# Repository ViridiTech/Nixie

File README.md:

# Nixie
 4 digit nixie clock on IN-12 lamps
 
</a>

General schematic inculed most important components:

</a>

Brain of the clock is [ESP32-C3 Super Mini](https://allegro.pl/events/clicks?emission_unit_id=f06a5ec8-8059-49f5-b3e1-0427a0f30828&emission_id=fa8220df-9dc3-44b3-8bd5-d7bab4bfcdd1&type=OFFER&ts=1741079374214&redirect=https%3A%2F%2Fallegro.pl%2Foferta%2Fesp32-c3-super-mini-wifi-bluetooth-ble-5-0-nastepca-esp8266-d1-mini-15295513744%3Fbi_s%3Dads%26bi_m%3Dproductlisting%253Adesktop%253Aquery%26bi_c%3DYjM1MWQ2YjgtZmRkYS00ZTU5LWE4YWEtZmFkNTI4YTliM2E3AA%26bi_t%3Dape&placement=productlisting:desktop:query&sig=47fc114a77d64e92962a4eec50b8c331).

ICs used:

- two 74HC959 shift registers,

- four nixie lamp drivers: K155ID1 and SN74141N both work the same and have the same I/O.

Four IN-12 display time. Both A and B variants could be used.

Seconds indicator is taken from probe screwdriver, typical neon indicator (gas-discharge lamp) can be used.

Seconds indicator is driven by 5V relay (transistor-diode control to ensure no damage to microcontroler should be used, or alternatively for DIY solution Arduino relay module can be used).

Nixie lamps require 170V power supply to be used, I chose [this one](https://pl.aliexpress.com/item/1005005721193065.html?src=google&pdp_npi=4%40dis!PLN!15.17!11.59!!!!!%40!12000034113964492!ppc!!!&src=google&albch=shopping&acnt=708-803-3821&isdl=y&slnk=&plac=&mtctp=&albbt=Google_7_shopping&aff_platform=google&aff_short_key=UneMJZVf&gclsrc=aw.ds&&albagn=888888&&ds_e_adid=&ds_e_matchtype=&ds_e_device=c&ds_e_network=x&ds_e_product_group_id=&ds_e_product_id=pl1005005721193065&ds_e_product_merchant_id=107726890&ds_e_product_country=PL&ds_e_product_language=pl&ds_e_product_channel=online&ds_e_product_store_id=&ds_url_v=2&albcp=19735245762&albag=&isSmbAutoCall=false&needSmbHouyi=false&gad_source=1&gclid=CjwKCAiA5pq-BhBuEiwAvkzVZf3OkaujjkBrAG5RaLtoEE9kd9NwcMxYW9DeDCp0z5XIMhVfqe0_oxoCYh0QAvD_BwE).

# IMPORTANT
You have to program ESP32 yourself using Arduino IDE or other ESP-compatible environment using NIXIE_clock directory.

In the code you MUST MODIFY WiFi settings to allow the clock to connect to the Internet.

# DISCLAIMER
The current code has not been tested on current version of hardware.

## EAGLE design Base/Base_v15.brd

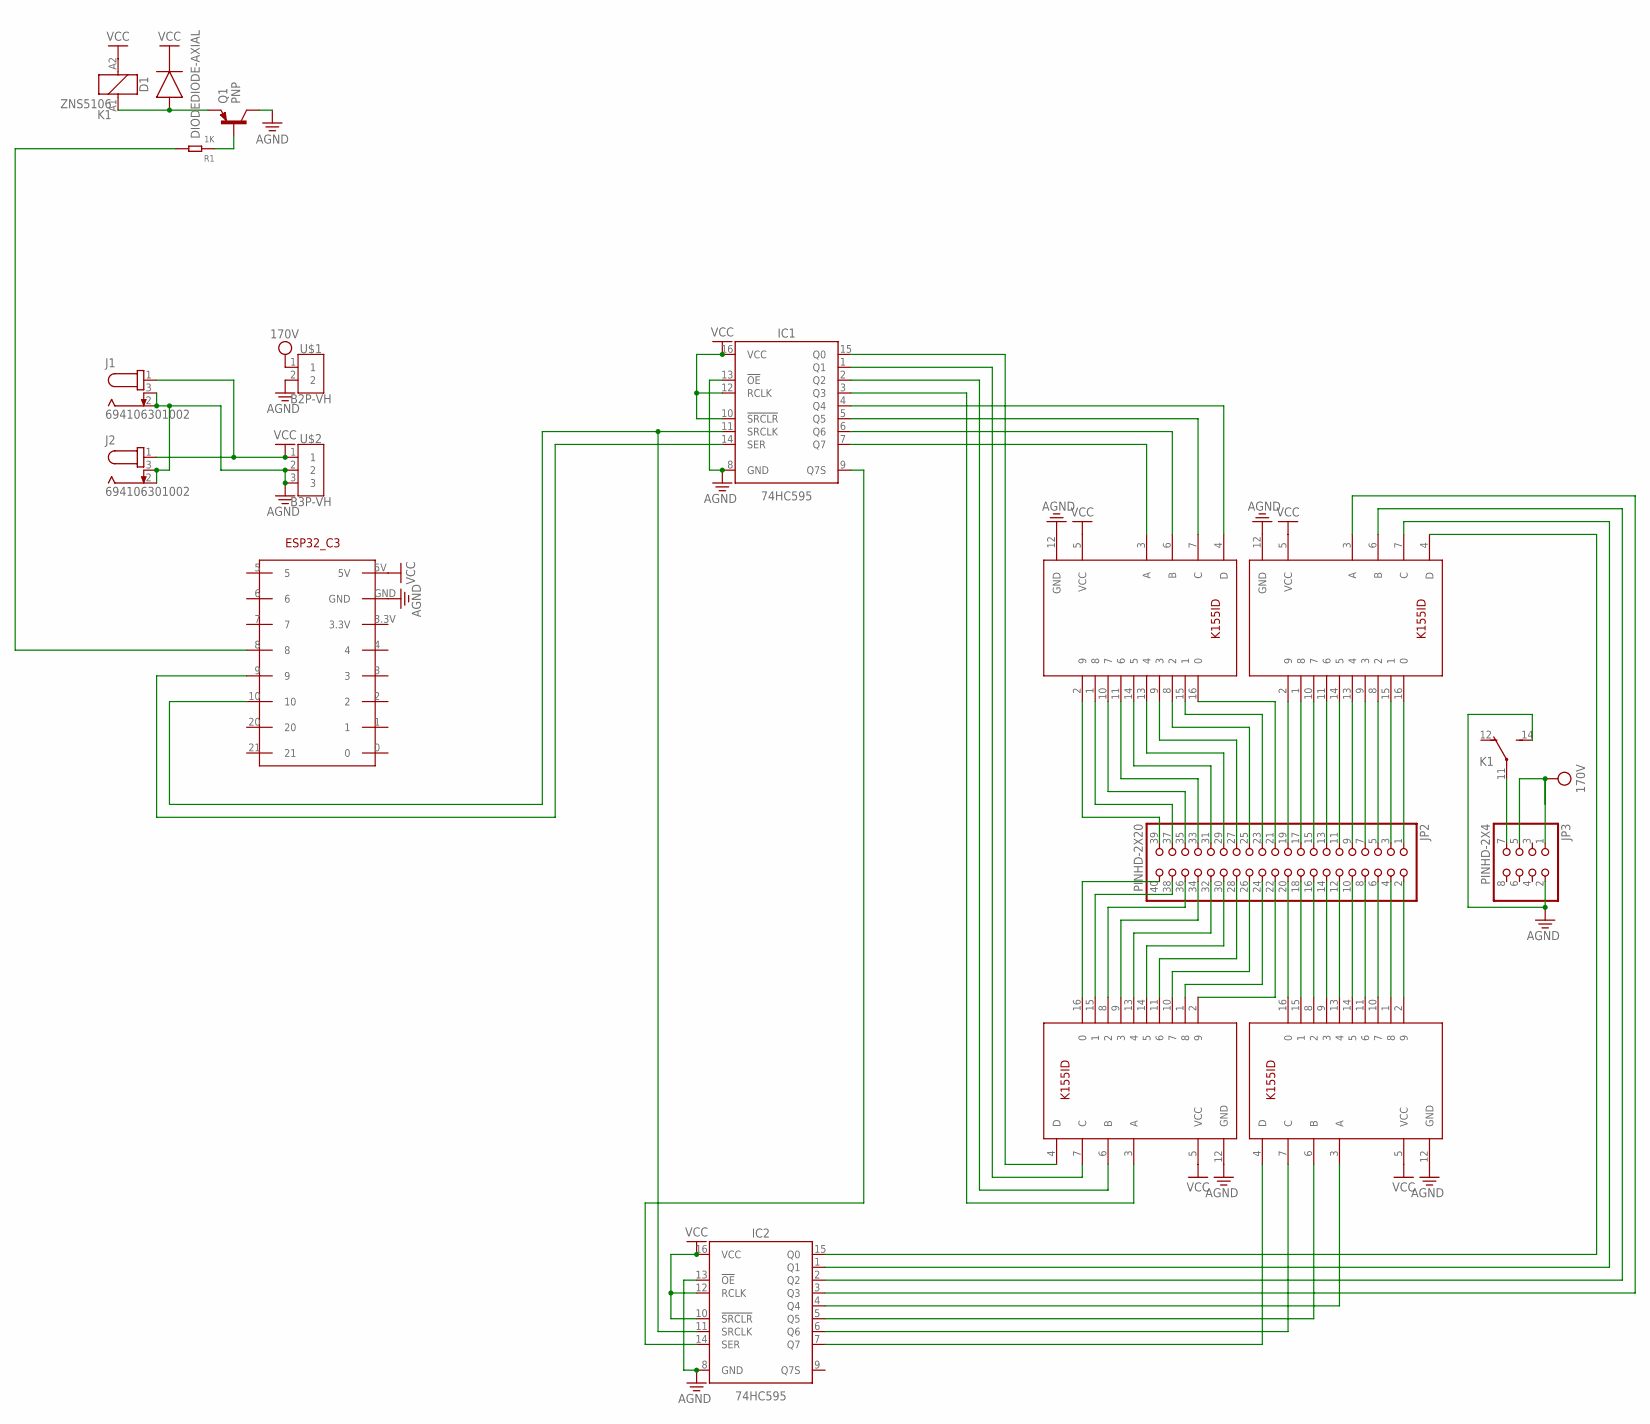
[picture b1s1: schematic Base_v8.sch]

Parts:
D1: DIODEDIODE-AXIAL; DIODE-AXIAL
IC1, IC2: 74HC595; DIP762W53P254L1969H508Q16B
IC3, IC4, IC5, IC6: K155ID
J1, J2: 694106301002
JP2: PINHD-2X20; 2X20
JP3: PINHD-2X4; 2X04
K1: ZNS5106; ZN5
Q1: PNP; TO92
R1: 1K; PR-D2.3XL6.5MM
U$1: B2P-VH; B2P-VH_396-2N
U$2: B3P-VH; B3P-VH_396_3N
U$5: ESP32_C3_SUPERMINI

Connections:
170V: JP3.1, JP3.5, U$1.1
AGND: IC1.8 (GND), IC1.13 (!OE), IC2.8 (GND), IC2.13 (!OE), IC3.12 (GND), IC4.12 (GND), IC5.12 (GND), IC6.12 (GND), J1.2, J1.3, J2.2, J2.3, JP3.2, K1.14 (S), Q1.1 (C), U$1.2, U$2.2, U$2.3, U$5.GND
unnamed: IC5.16 (0), JP2.1
unnamed: IC5.15 (1), JP2.3
unnamed: IC5.8 (2), JP2.5
unnamed: IC5.9 (3), JP2.7
unnamed: IC5.13 (4), JP2.9
unnamed: IC5.14 (5), JP2.11
unnamed: IC5.11 (6), JP2.13
unnamed: IC5.10 (7), JP2.15
unnamed: IC5.1 (8), JP2.17
unnamed: IC5.2 (9), JP2.19
unnamed: IC3.16 (0), JP2.21
unnamed: IC3.15 (1), JP2.23
unnamed: IC3.8 (2), JP2.25
unnamed: IC3.9 (3), JP2.27
unnamed: IC3.13 (4), JP2.29
unnamed: IC3.14 (5), JP2.31
unnamed: IC3.11 (6), JP2.33
unnamed: IC3.10 (7), JP2.35
unnamed: IC3.1 (8), JP2.37
unnamed: IC3.2 (9), JP2.39
unnamed: IC6.2 (9), JP2.2
unnamed: IC6.1 (8), JP2.4
unnamed: IC6.10 (7), JP2.6
unnamed: IC6.11 (6), JP2.8
unnamed: IC6.14 (5), JP2.10
unnamed: IC6.13 (4), JP2.12
unnamed: IC6.9 (3), JP2.14
unnamed: IC6.8 (2), JP2.16
unnamed: IC6.15 (1), JP2.18
unnamed: IC6.16 (0), JP2.20
unnamed: IC4.16 (0), JP2.40
unnamed: IC4.15 (1), JP2.38
unnamed: IC4.8 (2), JP2.36
unnamed: IC4.9 (3), JP2.34
unnamed: IC4.13 (4), JP2.32
unnamed: IC4.14 (5), JP2.30
unnamed: IC4.11 (6), JP2.28
unnamed: IC4.10 (7), JP2.26
unnamed: IC4.1 (8), JP2.24
unnamed: IC4.2 (9), JP2.22
unnamed: IC1.15 (Q0), IC4.4 (D)
unnamed: IC1.1 (Q1), IC4.7 (C)
unnamed: IC1.2 (Q2), IC4.6 (B)
unnamed: IC1.3 (Q3), IC4.3 (A)
unnamed: IC2.4 (Q4), IC6.3 (A)
unnamed: IC2.5 (Q5), IC6.6 (B)
unnamed: IC2.6 (Q6), IC6.7 (C)
unnamed: IC2.7 (Q7), IC6.4 (D)
unnamed: IC1.7 (Q7), IC3.3 (A)
unnamed: IC1.6 (Q6), IC3.6 (B)
unnamed: IC1.5 (Q5), IC3.7 (C)
unnamed: IC1.4 (Q4), IC3.4 (D)
unnamed: IC2.15 (Q0), IC5.4 (D)
unnamed: IC2.1 (Q1), IC5.7 (C)
unnamed: IC2.2 (Q2), IC5.6 (B)
unnamed: IC2.3 (Q3), IC5.3 (A)
unnamed: IC1.9 (Q7S), IC2.14 (SER)
unnamed: IC1.14 (SER), U$5.9
unnamed: D1.1 (A), K1.A1 (1), Q1.3 (E)
unnamed: Q1.2 (B), R1.1
unnamed: R1.2, U$5.8
unnamed: JP3.7, K1.11

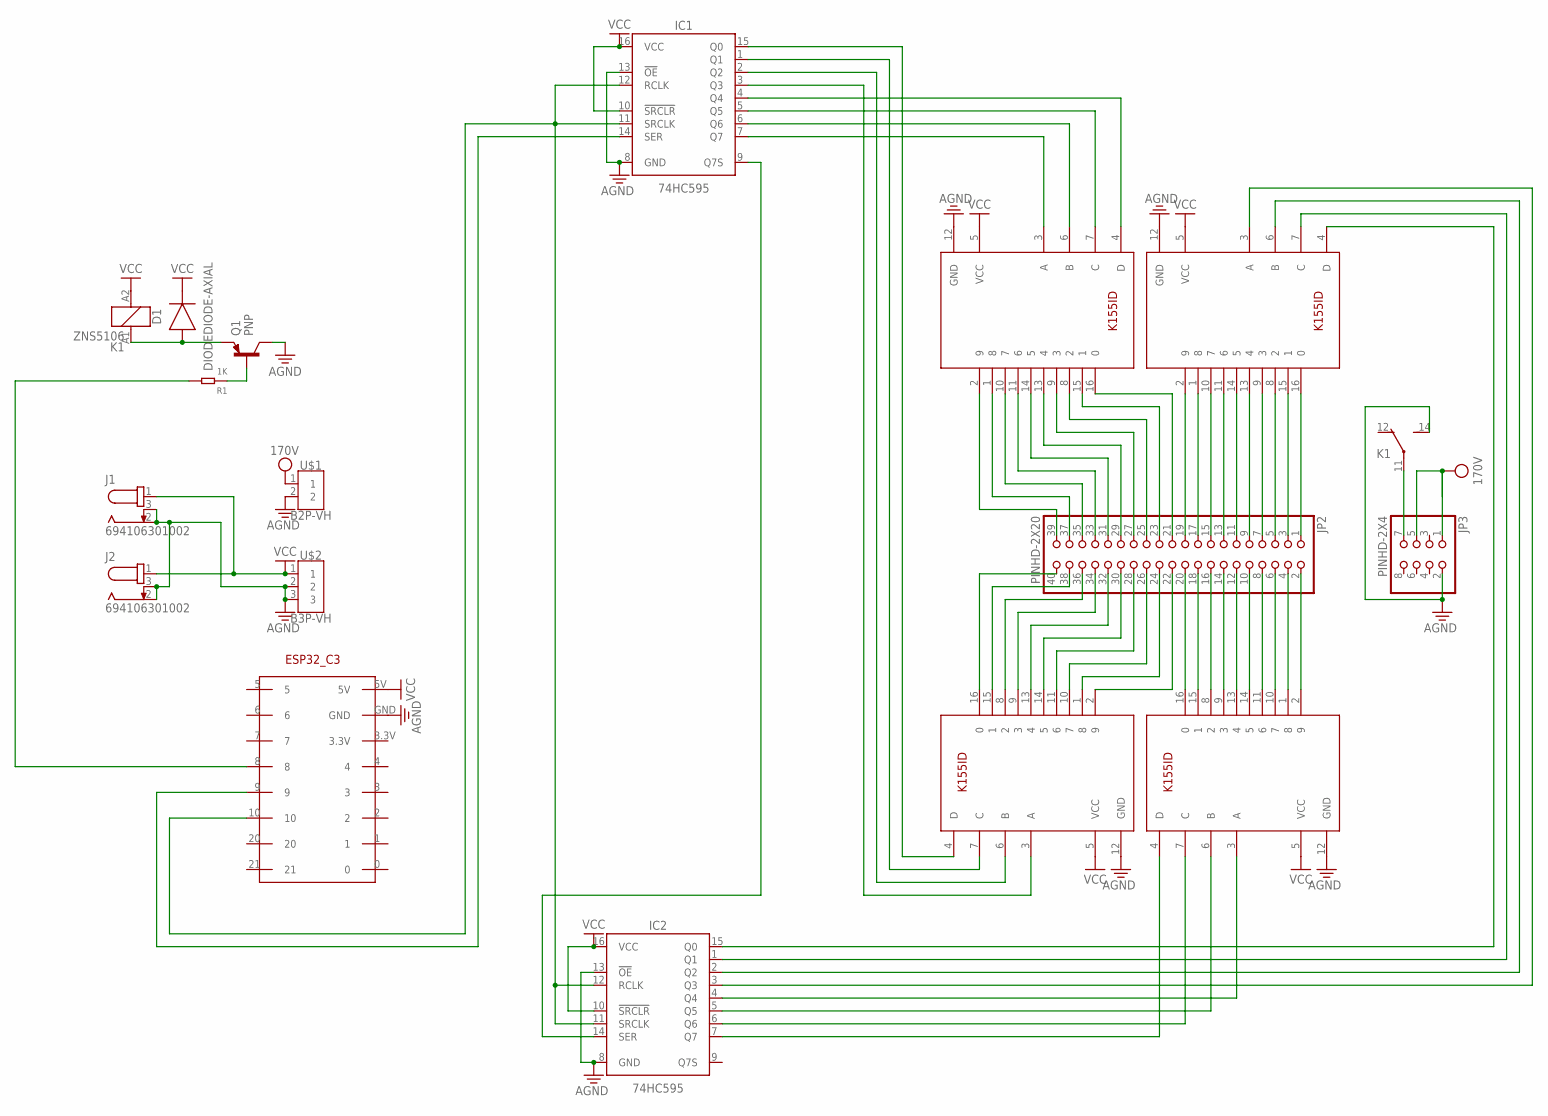
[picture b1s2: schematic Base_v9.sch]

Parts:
D1: DIODEDIODE-AXIAL; DIODE-AXIAL
IC1, IC2: 74HC595; DIP762W53P254L1969H508Q16B
IC3, IC4, IC5, IC6: K155ID
J1, J2: 694106301002
JP2: PINHD-2X20; 2X20
JP3: PINHD-2X4; 2X04
K1: ZNS5106; ZN5
Q1: PNP; TO92
R1: 1K; PR-D2.3XL6.5MM
U$1: B2P-VH; B2P-VH_396-2N
U$2: B3P-VH; B3P-VH_396_3N
U$5: ESP32_C3_SUPERMINI

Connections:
170V: JP3.1, JP3.5, U$1.1
AGND: IC1.8 (GND), IC1.13 (!OE), IC2.8 (GND), IC2.13 (!OE), IC3.12 (GND), IC4.12 (GND), IC5.12 (GND), IC6.12 (GND), J1.2, J1.3, J2.2, J2.3, JP3.2, K1.14 (S), Q1.1 (C), U$1.2, U$2.2, U$2.3, U$5.GND
unnamed: IC5.16 (0), JP2.1
unnamed: IC5.15 (1), JP2.3
unnamed: IC5.8 (2), JP2.5
unnamed: IC5.9 (3), JP2.7
unnamed: IC5.13 (4), JP2.9
unnamed: IC5.14 (5), JP2.11
unnamed: IC5.11 (6), JP2.13
unnamed: IC5.10 (7), JP2.15
unnamed: IC5.1 (8), JP2.17
unnamed: IC5.2 (9), JP2.19
unnamed: IC3.16 (0), JP2.21
unnamed: IC3.15 (1), JP2.23
unnamed: IC3.8 (2), JP2.25
unnamed: IC3.9 (3), JP2.27
unnamed: IC3.13 (4), JP2.29
unnamed: IC3.14 (5), JP2.31
unnamed: IC3.11 (6), JP2.33
unnamed: IC3.10 (7), JP2.35
unnamed: IC3.1 (8), JP2.37
unnamed: IC3.2 (9), JP2.39
unnamed: IC6.2 (9), JP2.2
unnamed: IC6.1 (8), JP2.4
unnamed: IC6.10 (7), JP2.6
unnamed: IC6.11 (6), JP2.8
unnamed: IC6.14 (5), JP2.10
unnamed: IC6.13 (4), JP2.12
unnamed: IC6.9 (3), JP2.14
unnamed: IC6.8 (2), JP2.16
unnamed: IC6.15 (1), JP2.18
unnamed: IC6.16 (0), JP2.20
unnamed: IC4.16 (0), JP2.40
unnamed: IC4.15 (1), JP2.38
unnamed: IC4.8 (2), JP2.36
unnamed: IC4.9 (3), JP2.34
unnamed: IC4.13 (4), JP2.32
unnamed: IC4.14 (5), JP2.30
unnamed: IC4.11 (6), JP2.28
unnamed: IC4.10 (7), JP2.26
unnamed: IC4.1 (8), JP2.24
unnamed: IC4.2 (9), JP2.22
unnamed: IC1.15 (Q0), IC4.4 (D)
unnamed: IC1.1 (Q1), IC4.7 (C)
unnamed: IC1.2 (Q2), IC4.6 (B)
unnamed: IC1.3 (Q3), IC4.3 (A)
unnamed: IC2.4 (Q4), IC6.3 (A)
unnamed: IC2.5 (Q5), IC6.6 (B)
unnamed: IC2.6 (Q6), IC6.7 (C)
unnamed: IC2.7 (Q7), IC6.4 (D)
unnamed: IC1.7 (Q7), IC3.3 (A)
unnamed: IC1.6 (Q6), IC3.6 (B)
unnamed: IC1.5 (Q5), IC3.7 (C)
unnamed: IC1.4 (Q4), IC3.4 (D)
unnamed: IC2.15 (Q0), IC5.4 (D)
unnamed: IC2.1 (Q1), IC5.7 (C)
unnamed: IC2.2 (Q2), IC5.6 (B)
unnamed: IC2.3 (Q3), IC5.3 (A)
unnamed: IC1.9 (Q7S), IC2.14 (SER)
unnamed: IC1.14 (SER), U$5.9
unnamed: D1.1 (A), K1.A1 (1), Q1.3 (E)
unnamed: Q1.2 (B), R1.1
unnamed: R1.2, U$5.8
unnamed: JP3.7, K1.11

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
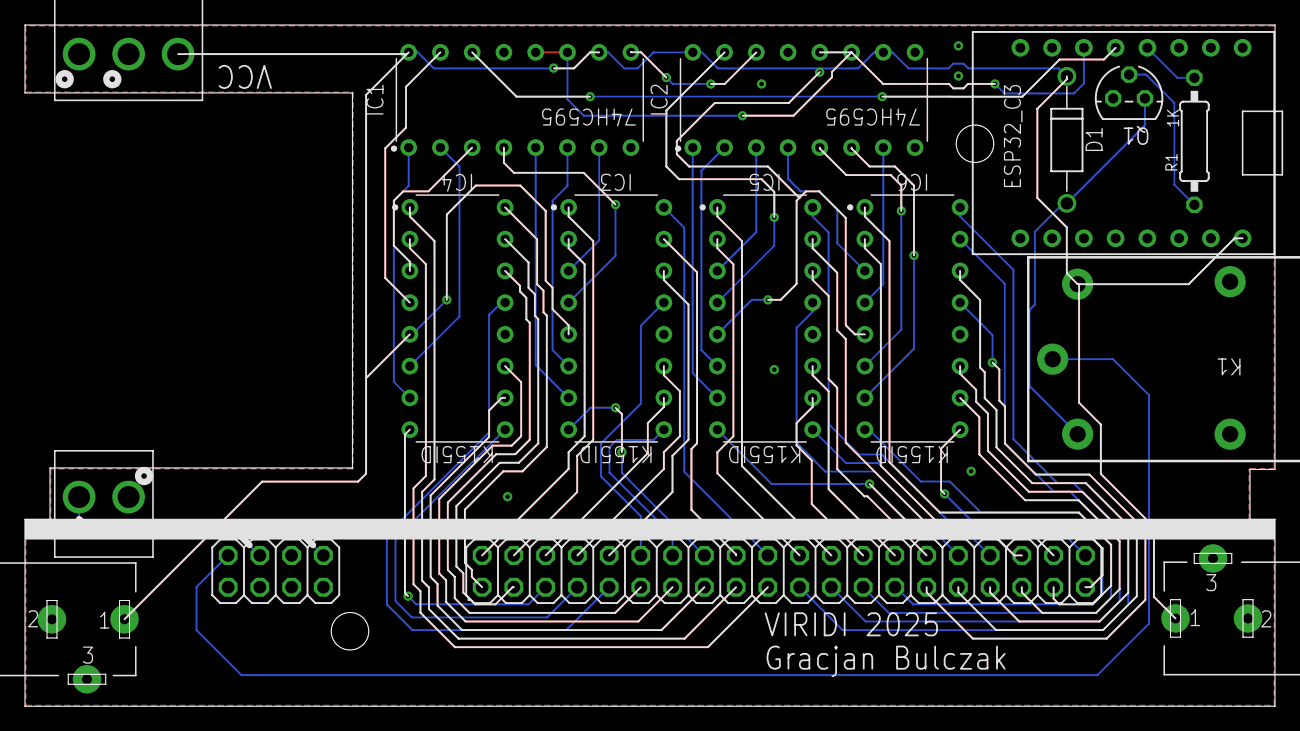
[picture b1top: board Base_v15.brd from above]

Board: 2 copper layers, 100.0 x 54.5 mm, 17 parts (0 on the bottom side), 66 nets.

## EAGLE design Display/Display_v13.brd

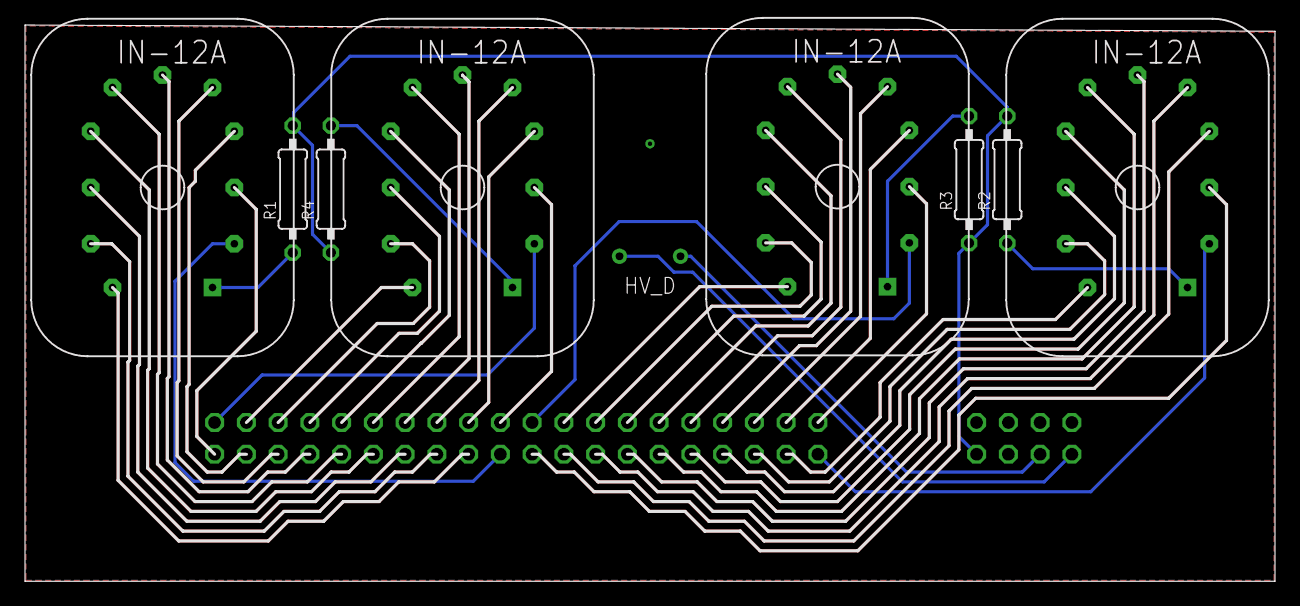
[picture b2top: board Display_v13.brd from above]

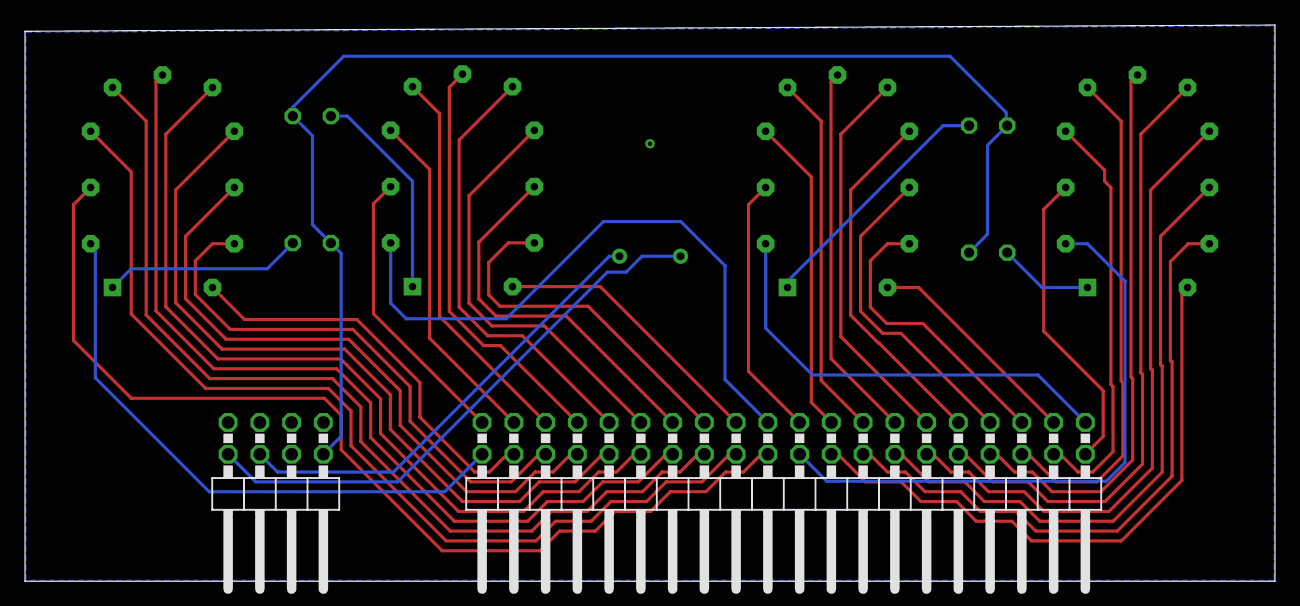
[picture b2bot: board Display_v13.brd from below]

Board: 2 copper layers, 100.0 x 44.5 mm, 11 parts (2 on the bottom side), 47 nets.

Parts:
HV_D: HV_D; XTALRR488W43L1135T465H1346B
JP1: PINHD-2X20/90; 2X20/90
JP2: PINHD-2X4/90; 2X04/90
R1, R2, R3, R4: 2.2K; PR-D2.3XL6.5MM
U$1, U$2, U$3, U$4: IN-12

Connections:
unnamed: JP1.23, U$4.P$1
unnamed: JP1.39, U$4.P$9
unnamed: JP1.4, U$1.P$8
unnamed: JP1.6, U$1.P$7
unnamed: JP1.40, U$2.P$10
unnamed: JP1.22, U$2.P$9
unnamed: JP1.19, U$3.P$9
unnamed: JP1.17, U$3.P$8
unnamed: JP1.15, U$3.P$7
unnamed: JP1.13, U$3.P$6
unnamed: JP1.11, U$3.P$5
unnamed: JP1.9, U$3.P$4
unnamed: JP1.7, U$3.P$3
unnamed: JP1.5, U$3.P$2
unnamed: JP1.3, U$3.P$1
unnamed: JP1.1, U$3.P$10
unnamed: HV_D.2, JP2.8
unnamed: HV_D.1, JP2.6
unnamed: JP1.14, U$1.P$3
unnamed: JP1.16, U$1.P$2
unnamed: R1.1, U$1.P$11
unnamed: R2.1, U$2.P$11
unnamed: R3.2, U$4.P$11
unnamed: R4.2, U$3.P$11
unnamed: JP2.2, R1.2, R2.2, R3.1, R4.1
unnamed: JP1.18, U$1.P$1
unnamed: JP1.20, U$1.P$10
unnamed: JP1.38, U$2.P$1
unnamed: JP1.36, U$2.P$2
unnamed: JP1.34, U$2.P$3
unnamed: JP1.24, U$2.P$8
unnamed: JP1.26, U$2.P$7
unnamed: JP1.28, U$2.P$6
unnamed: JP1.30, U$2.P$5
unnamed: JP1.32, U$2.P$4
unnamed: JP1.2, U$1.P$9
unnamed: JP1.8, U$1.P$6
unnamed: JP1.10, U$1.P$5
unnamed: JP1.12, U$1.P$4
unnamed: JP1.37, U$4.P$8
unnamed: JP1.35, U$4.P$7
unnamed: JP1.33, U$4.P$6
unnamed: JP1.31, U$4.P$5
unnamed: JP1.29, U$4.P$4
unnamed: JP1.27, U$4.P$3
unnamed: JP1.25, U$4.P$2
unnamed: JP1.21, U$4.P$10

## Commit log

2025-02-21 bulk upload
2025-02-21 STEP file and 3D manufacturing file upload
2025-03-04 Resolved switched pins issue
2025-03-04 Added general schematic for DIY makers
2025-03-04 Fixed shift register clock lines
2025-03-04 General schematic for DIY makers
2025-03-04 Added ESP32 program [.ino]
